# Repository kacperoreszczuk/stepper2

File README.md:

# stepper2
Second version of the lums stepper

Compiling in STM32CubeIDE:

0. Disclaimer: STM32CubeIDE constantly invents new ways to make this instruction not work. Be mentally prepared that you will have to bruteforce this with LLM anyway.
1. Install STM32CubeIDE, sadly requires account creation
2. Click "Import project" and select "fw" directory from this repository
3. In the "Project Explorer" panel on the left open stepper2.ioc
    - confirm "open associated perspecitve" if prompted
    - continue with the current version of the firmware if prompted (do not migrate)
    - Login into MyST account if prompted
    - if not prompted and you get problems later in the instruction in point 4  (more precisely "this project is not a CDT project") then in the stepper2.ioc window click Help->Configuration Tool->Manage Embedded Software Libraries, scroll to STM32H7 and check tick box near version 1.11.1. Click Install. Hopefully you will be prompted to login and the package will install. Continue with instruction (starting here with Project->Generate Code)
    - in the top menu select Project->Generate Code
    - confirm "open associated perspecitve" if prompted
4. go to Project -> Properties -> C/C++ Build -> Settings
    - if "Properties" button is inactive click on main.c file subwindow to focus on it
    - in MCU(or MCU/MPU) Settings  check both "Use float..." options
    - in "MCU Post build outputs" enable binary file (or "convert to binary file")
    - in MCU(or MCU/MPU) GCC Compiler->Optimization: change level to -O3
    - in MCU(or MCU/MPU) G++ Compiler->Optimization: change level to -O3
    - If you want to switch to release configuration, change configuration to Release in the top of the Settings window, and repeat last four steps. In that case take care to build in the release later.
    - click apply and close, confirm if prompted to rebuild index
5. You may want to go to Core/Inc/defaults.hpp and change #define DRIVER_ID to a different value (any you like), especially if you would use more than one device simultaneously and want to be able to discern between them when talking through serial port.
6. Power up the driver and connect it with micro usb port (near the power input socket, slightly lower). Click Run->Run or click the green arrow icon to build and flash the device.
    - You may be prompted to upgrade the stlink firmware. Agree. In the STLinkUpgrade Window click "Open in update mode" and then "Upgrade". Unplug and plug the micro USB cable and try again number 6 in this instruction.
    - you may be prompted to save the files you edited. Agree.
7. Alternatively to point 6. you can select Project->Build Project and then copy manually the file in Debug/stepper2.bin to the mass storage device that opens after conneting the driver.

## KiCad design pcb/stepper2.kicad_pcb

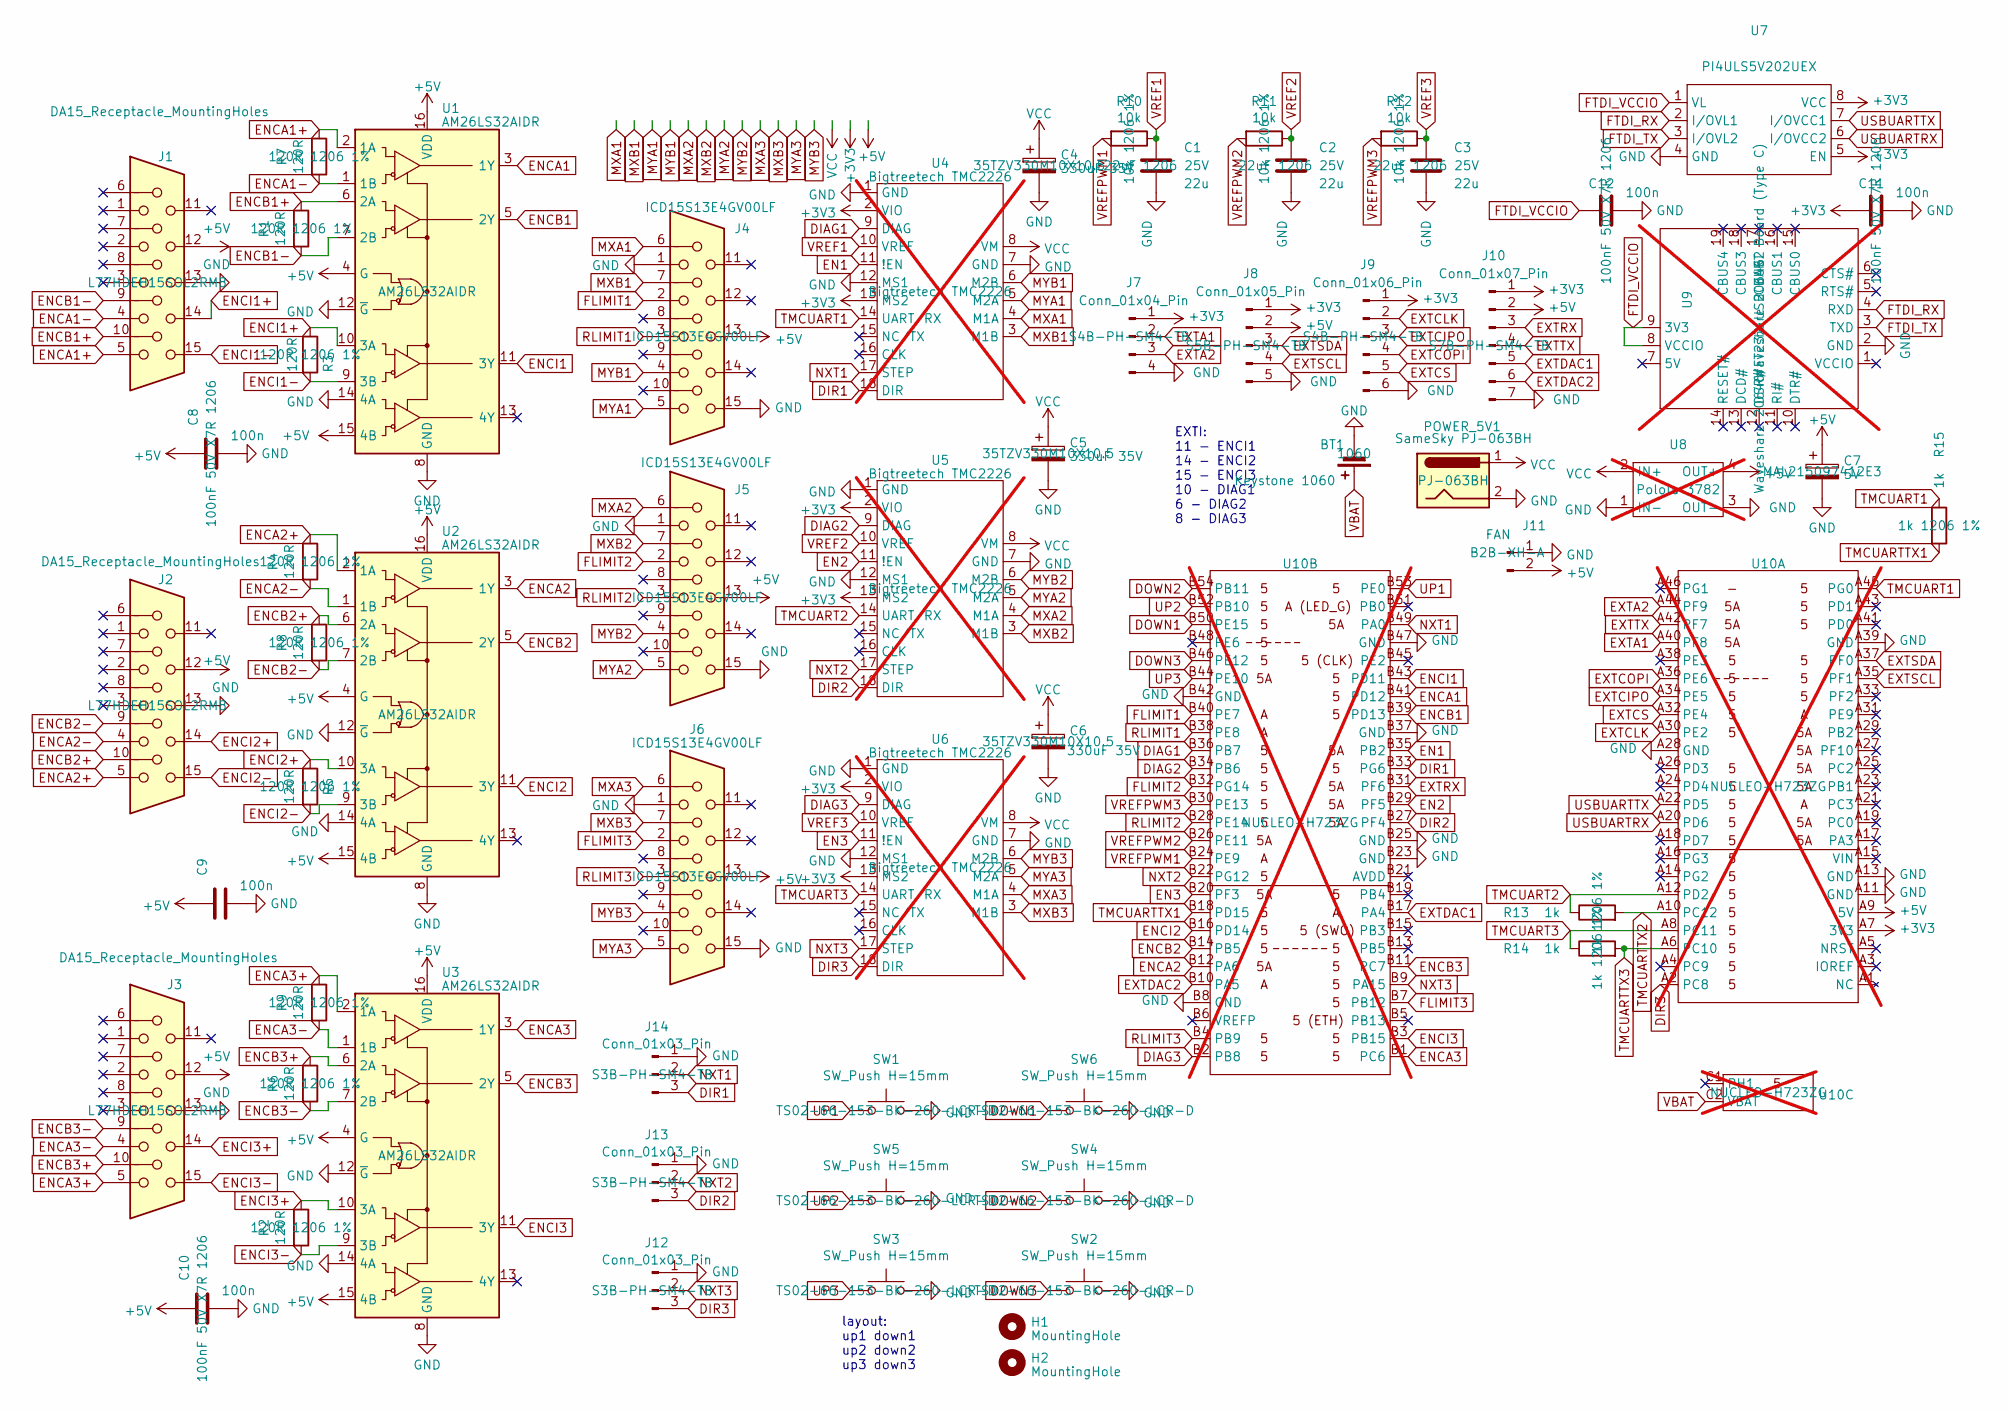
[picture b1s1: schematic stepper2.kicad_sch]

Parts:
BT1: Keystone 1060; BatteryHolder_Keystone_1060_1x2032; mpn 1060
C1, C2, C3: 22u; C_1206_3216Metric_Pad1.33x1.80mm_HandSolder; mpn 22uF 1206 25V; LCSC C12891
C4, C5, C6: 330uF 35V; CP_Elec_10x10.5; mpn 35TZV330M10X10.5; LCSC C2880403
C7: 5V; CP_Elec_8x10.5; mpn MAL215097412E3; LCSC C310836
C8, C9, C10, C11, C12: 100n; C_1206_3216Metric_Pad1.33x1.80mm_HandSolder; mpn 100nF 50V X7R 1206; LCSC C24497
H1, H2: MountingHole; MountingHole_3.2mm_M3
J1, J2, J3: DA15_Receptacle_MountingHoles; DSUB-15-HD_Vertical_Pitch2.29x1.98mm_Mercury3000_Enc; mpn L77HDEH15SOL2RM8
J4, J5, J6: ICD15S13E4GV00LF; DSUB-15-HD_Horizontal_Pitch2.29x2.54mm_EdgePinOffset9.40mm; mpn ICD15S13E4GV00LF
J7: Conn_01x04_Pin; JST_PH_S4B-PH-SM4-TB_1x04-1MP_P2.00mm_Horizontal; mpn S4B-PH-SM4-TB; LCSC C265102
J8: Conn_01x05_Pin; JST_PH_S5B-PH-SM4-TB_1x05-1MP_P2.00mm_Horizontal; mpn S5B-PH-SM4-TB; LCSC C265104
J9: Conn_01x06_Pin; JST_PH_S6B-PH-SM4-TB_1x06-1MP_P2.00mm_Horizontal; mpn S4B-PH-SM4-TB; LCSC C265405
J10: Conn_01x07_Pin; JST_PH_S7B-PH-SM4-TB_1x07-1MP_P2.00mm_Horizontal; mpn S7B-PH-SM4-TB; LCSC C265453
J11: FAN; JST_XH_B2B-XH-AM_1x02_P2.50mm_Vertical; mpn B2B-XH-A
J12, J13, J14: Conn_01x03_Pin; JST_PH_S3B-PH-SM4-TB_1x03-1MP_P2.00mm_Horizontal; mpn S3B-PH-SM4-TB; LCSC C265101
POWER_5V1: SameSky PJ-063BH; BarrelJack_CUI_PJ-063AH_Horizontal_CircularHoles; mpn PJ-063BH
R1, R2, R3, R4, R5, R6, R7, R8, R9: 120R; R_1206_3216Metric_Pad1.30x1.75mm_HandSolder; mpn 120R 1206 1%; LCSC C17909
R10, R11, R12: 10k; R_1206_3216Metric_Pad1.30x1.75mm_HandSolder; mpn 10k 1206 1%; LCSC C17902
R13, R14, R15: 1k; R_1206_3216Metric_Pad1.30x1.75mm_HandSolder; mpn 1k 1206 1%; LCSC C4410
SW1, SW2, SW3, SW4, SW5, SW6: SW_Push H=15mm; SW_PUSH_6mm_H4.3mm; mpn TS02-66-153-BK-260-LCR-D
U1, U2, U3: AM26LS32AIDR; SO-16_3.9x9.9mm_P1.27mm; mpn AM26LS32AIDR; LCSC C19092
U4, U5, U6: Bigtreetech TMC2226; TMC2209_BIGTREETECH; mpn Bigtreetech TMC2226; not fitted
U7: MSOP-8_3x3mm_P0.65mm; mpn PI4ULS5V202UEX; LCSC C481697
U8: POLOLU_3782; mpn Pololu 3782; not fitted
U9: Waveshare 20646 FT232 USB UART Board (Type C); Waveshare_FT232_USBC_module; mpn Waveshare 20646; not fitted
U10: Nucleo144_H723_withVBAT; mpn NUCLEO-H723ZG; not fitted

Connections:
+3V3: C11.1, J7.1, J8.1, J9.1, J10.1, U4.2 (VIO), U4.13 (MS2), U5.2 (VIO), U5.13 (MS2), U6.2 (VIO), U6.13 (MS2), U7.5 (EN), U7.8 (VCC), U10.A7 (3V3)
+5V: C7.1, C8.1, C9.1, C10.1, J1.12, J2.12, J3.12, J4.13, J5.13, J6.13, J8.2, J10.2, J11.2, U1.4 (G), U1.15 (4B), U1.16 (VDD), U2.4 (G), U2.15 (4B), U2.16 (VDD), U3.4 (G), U3.15 (4B), U3.16 (VDD), U8.4 (OUT+), U10.A9 (5V)
DIAG1: U4.9 (DIAG), U10.B36 (PB7)
DIAG2: U5.9 (DIAG), U10.B34 (PB6)
DIAG3: U6.9 (DIAG), U10.B2 (PB8)
DIR1: J14.3, U4.18 (DIR), U10.B33 (PG6)
DIR2: J13.3, U5.18 (DIR), U10.B27 (PF4)
DIR3: J12.3, U6.18 (DIR), U10.A2 (PC8)
DOWN1: SW6.1, U10.B50 (PE15)
DOWN2: SW4.1, U10.B54 (PB11)
DOWN3: SW2.1, U10.B46 (PE12)
EN1: U4.11 (!EN), U10.B35 (PB2)
EN2: U5.11 (!EN), U10.B29 (PF5)
EN3: U6.11 (!EN), U10.B20 (PF3)
ENCA1: U1.3 (1Y), U10.B41 (PD12)
ENCA1+: J1.5, R7.1, U1.2 (1A)
ENCA1-: J1.4, R7.2, U1.1 (1B)
ENCA2: U2.3 (1Y), U10.B12 (PA6)
ENCA2+: J2.5, R4.1, U2.2 (1A)
ENCA2-: J2.4, R4.2, U2.1 (1B)
ENCA3: U3.3 (1Y), U10.B1 (PC6)
ENCA3+: J3.5, R9.1, U3.2 (1A)
ENCA3-: J3.4, R9.2, U3.1 (1B)
ENCB1: U1.5 (2Y), U10.B39 (PD13)
ENCB1+: J1.10, R1.1, U1.6 (2A)
ENCB1-: J1.9, R1.2, U1.7 (2B)
ENCB2: U2.5 (2Y), U10.B14 (PB5)
ENCB2+: J2.10, R8.1, U2.6 (2A)
ENCB2-: J2.9, R8.2, U2.7 (2B)
ENCB3: U3.5 (2Y), U10.B11 (PC7)
ENCB3+: J3.10, R6.1, U3.6 (2A)
ENCB3-: J3.9, R6.2, U3.7 (2B)
ENCI1: U1.11 (3Y), U10.B43 (PD11)
ENCI1+: J1.14, R3.1, U1.10 (3A)
ENCI1-: J1.15, R3.2, U1.9 (3B)
ENCI2: U2.11 (3Y), U10.B16 (PD14)
ENCI2+: J2.14, R5.1, U2.10 (3A)
ENCI2-: J2.15, R5.2, U2.9 (3B)
ENCI3: U3.11 (3Y), U10.B3 (PB15)
ENCI3+: J3.14, R2.1, U3.10 (3A)
ENCI3-: J3.15, R2.2, U3.9 (3B)
EXTA1: J7.2, U10.A40 (PF8)
EXTA2: J7.3, U10.A44 (PF9)
EXTCIPO: J9.3, U10.A34 (PE5)
EXTCLK: J9.2, U10.A30 (PE2)
EXTCOPI: J9.4, U10.A36 (PE6)
EXTCS: J9.5, U10.A32 (PE4)
EXTDAC1: J10.5, U10.B17 (PA4)
EXTDAC2: J10.6, U10.B10 (PA5)
EXTRX: J10.3, U10.B31 (PF6)
EXTSCL: J8.4, U10.A35 (PF1)
EXTSDA: J8.3, U10.A37 (PF0)
EXTTX: J10.4, U10.A42 (PF7)
FLIMIT1: J4.2, U10.B40 (PE7)
FLIMIT2: J5.2, U10.B32 (PG14)
FLIMIT3: J6.2, U10.B7 (PB12)
FTDI_RX: U7.2 (I/OVL1), U9.4 (RXD)
FTDI_TX: U7.3 (I/OVL2), U9.3 (TXD)
FTDI_VCCIO: C12.1, U7.1 (VL), U9.8 (VCCIO), U9.9 (3V3)
GND: BT1.2 (-), C1.2, C2.2, C3.2, C4.2, C5.2, C6.2, C7.2, C8.2, C9.2, C10.2, C11.2, C12.2, J1.13, J2.13, J3.13, J4.1, J4.15, J5.1, J5.15, J6.1, J6.15, J7.4, J8.5, J9.6, J10.7, J11.1, J12.1, J13.1, J14.1, POWER_5V1.2, SW1.2, SW2.2, SW3.2, SW4.2, SW5.2, SW6.2, U1.8 (GND), U1.12 (~G), U1.14 (4A), U2.8 (GND), U2.12 (~G), U2.14 (4A), U3.8 (GND), U3.12 (~G), U3.14 (4A), U4.1 (GND), U4.7 (GND), U4.12 (MS1), U5.1 (GND), U5.7 (GND), U5.12 (MS1), U6.1 (GND), U6.7 (GND), U6.12 (MS1), U7.4 (GND), U8.1 (IN-), U8.3 (OUT-), U9.2 (GND), U10.A11 (GND), U10.A13 (GND), U10.A28 (GND), U10.A39 (GND), U10.B8 (GND), U10.B23 (GND), U10.B25 (GND), U10.B37 (GND), U10.B42 (GND), U10.B47 (GND)
MXA1: J4.6, U4.4 (M1A)
MXA2: J5.6, U5.4 (M1A)
MXA3: J6.6, U6.4 (M1A)
MXB1: J4.7, U4.3 (M1B)
MXB2: J5.7, U5.3 (M1B)
MXB3: J6.7, U6.3 (M1B)
MYA1: J4.5, U4.5 (M2A)
MYA2: J5.5, U5.5 (M2A)
MYA3: J6.5, U6.5 (M2A)
MYB1: J4.4, U4.6 (M2B)
MYB2: J5.4, U5.6 (M2B)
MYB3: J6.4, U6.6 (M2B)
NXT1: J14.2, U4.17 (STEP), U10.B49 (PA0)
NXT2: J13.2, U5.17 (STEP), U10.B22 (PG12)
NXT3: J12.2, U6.17 (STEP), U10.B9 (PA15)
RLIMIT1: J4.3, U10.B38 (PE8)
RLIMIT2: J5.3, U10.B28 (PE14)
RLIMIT3: J6.3, U10.B4 (PB9)
TMCUART1: R15.1, U4.14 (UART/RX), U10.A45 (PG0)
TMCUART2: R13.1, U5.14 (UART/RX), U10.A12 (PD2)
TMCUART3: R14.1, U6.14 (UART/RX), U10.A8 (PC11)
TMCUARTTX1: R15.2, U10.B18 (PD15)
TMCUARTTX2: R13.2, U10.A10 (PC12)
TMCUARTTX3: R14.2, U10.A6 (PC10)
UP1: SW1.1, U10.B53 (PE0)
UP2: SW5.1, U10.B52 (PB10)
UP3: SW3.1, U10.B44 (PE10)
USBUARTRX: U7.6 (I/OVCC2), U10.A20 (PD6)
USBUARTTX: U7.7 (I/OVCC1), U10.A22 (PD5)
VBAT: BT1.1 (+), U10.C2 (VBAT)
VCC: C4.1, C5.1, C6.1, POWER_5V1.1, U4.8 (VM), U5.8 (VM), U6.8 (VM), U8.2 (IN+)
VREF1: C1.1, R10.1, U4.10 (VREF)
VREF2: C2.1, R11.1, U5.10 (VREF)
VREF3: C3.1, R12.1, U6.10 (VREF)
VREFPWM1: R10.2, U10.B24 (PE9)
VREFPWM2: R11.2, U10.B26 (PE11)
VREFPWM3: R12.2, U10.B30 (PE13)

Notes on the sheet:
layout: up1 down1 up2 down2 up3 down3
EXTI: 11 - ENCI1 14 - ENCI2 15 - ENCI3 10 - DIAG1 6 - DIAG2 8 - DIAG3

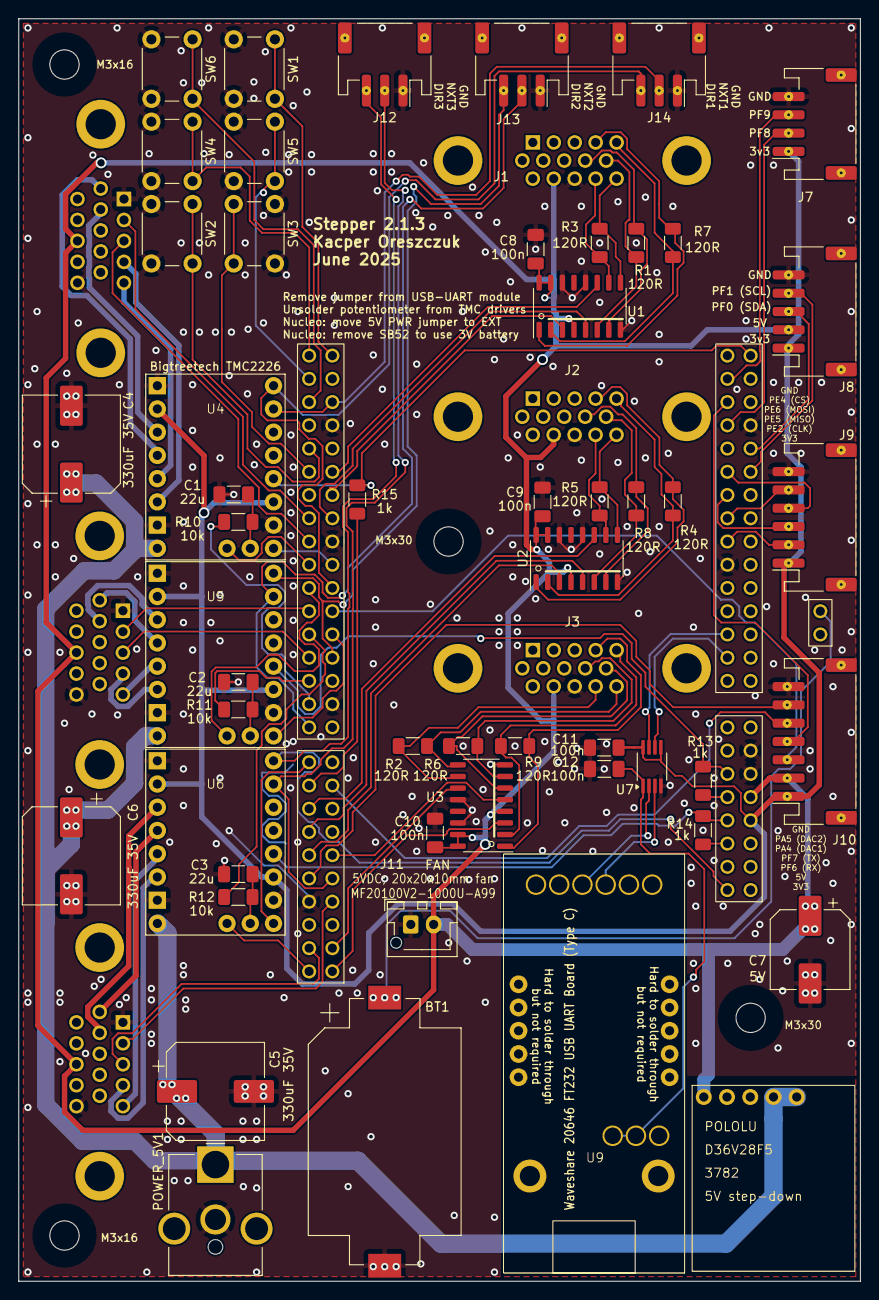
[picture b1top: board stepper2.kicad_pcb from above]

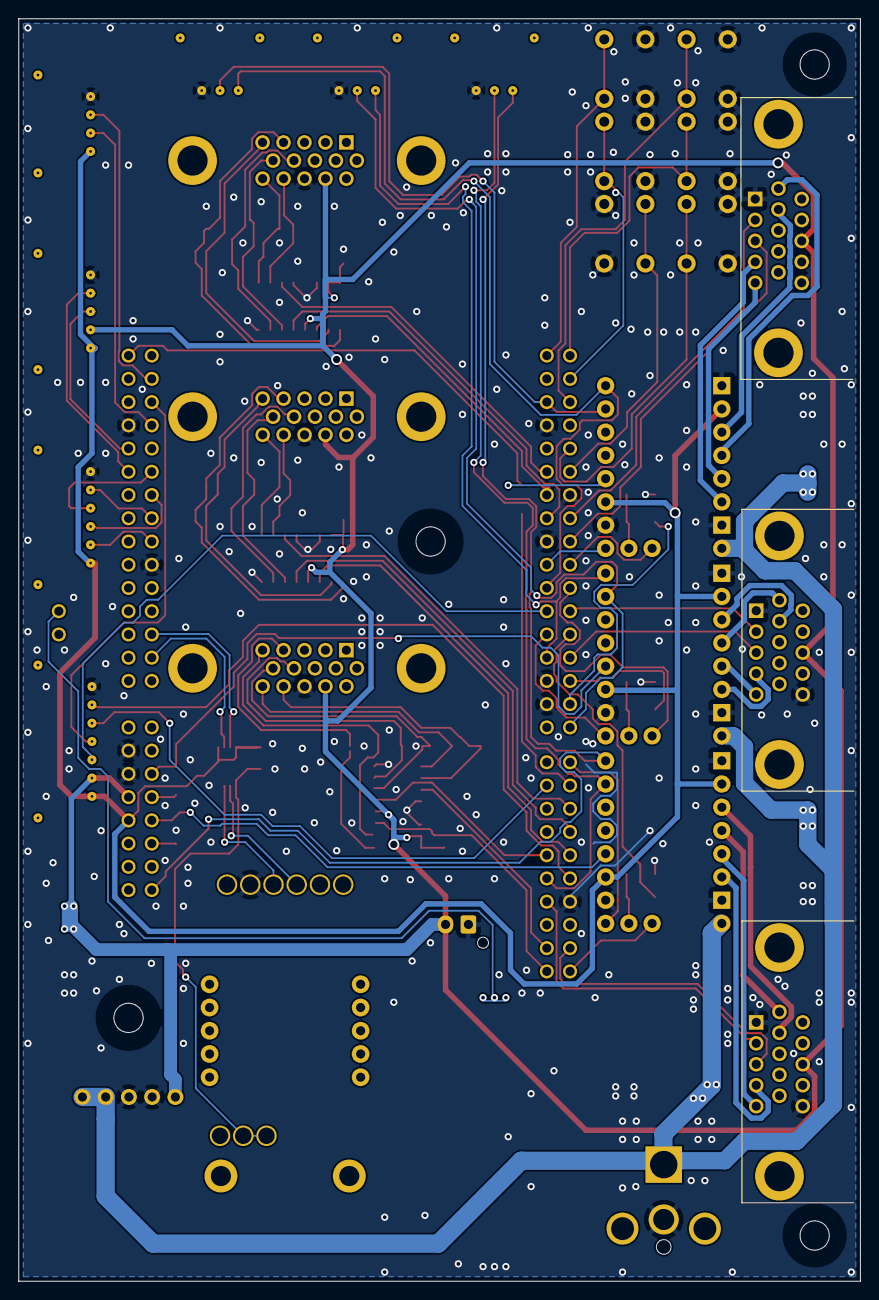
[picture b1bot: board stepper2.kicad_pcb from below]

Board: 2 copper layers, 92.0 x 138.0 mm, 61 parts (3 on the bottom side), 97 nets.

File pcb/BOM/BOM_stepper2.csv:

Comment,Designator,Footprint,LCSC
3V,BT1,Battery:BatteryHolder_Keystone_1060_1x2032,
22u,C1,Capacitor_SMD:C_1206_3216Metric_Pad1.33x1.80mm_HandSolder,C12891
22u,C2,Capacitor_SMD:C_1206_3216Metric_Pad1.33x1.80mm_HandSolder,C12891
22u,C3,Capacitor_SMD:C_1206_3216Metric_Pad1.33x1.80mm_HandSolder,C12891
24V,C4,Capacitor_SMD:CP_Elec_10x10.5,C5155335
24V,C5,Capacitor_SMD:CP_Elec_10x10.5,C5155335
24V,C6,Capacitor_SMD:CP_Elec_10x10.5,C5155335
5V,C7,Capacitor_SMD:CP_Elec_8x10.5,C310836
100n,C8,Capacitor_SMD:C_1206_3216Metric_Pad1.33x1.80mm_HandSolder,C24497
100n,C9,Capacitor_SMD:C_1206_3216Metric_Pad1.33x1.80mm_HandSolder,C24497
100n,C10,Capacitor_SMD:C_1206_3216Metric_Pad1.33x1.80mm_HandSolder,C24497
100n,C11,Capacitor_SMD:C_1206_3216Metric_Pad1.33x1.80mm_HandSolder,C24497
100n,C12,Capacitor_SMD:C_1206_3216Metric_Pad1.33x1.80mm_HandSolder,C24497
MountingHole,H1,stepper2:MountingHole_3.2mm_M3,
MountingHole,H2,stepper2:MountingHole_3.2mm_M3,
DA15_Receptacle_MountingHoles,J1,stepper2:DSUB-15-HD_Vertical_Pitch2.29x1.98mm_Mercury3000_Enc,
DA15_Receptacle_MountingHoles,J2,stepper2:DSUB-15-HD_Vertical_Pitch2.29x1.98mm_Mercury3000_Enc,
DA15_Receptacle_MountingHoles,J3,stepper2:DSUB-15-HD_Vertical_Pitch2.29x1.98mm_Mercury3000_Enc,
DE15_Receptacle_HighDensity,J4,stepper2:DSUB-15-HD_Horizontal_Pitch2.29x2.54mm_EdgePinOffset9.40mm,
DE15_Receptacle_HighDensity,J5,stepper2:DSUB-15-HD_Horizontal_Pitch2.29x2.54mm_EdgePinOffset9.40mm,
DE15_Receptacle_HighDensity,J6,stepper2:DSUB-15-HD_Horizontal_Pitch2.29x2.54mm_EdgePinOffset9.40mm,
Conn_01x04_Pin,J7,stepper2:JST_PH_S4B-PH-SM4-TB_1x04-1MP_P2.00mm_Horizontal,C265102
Conn_01x05_Pin,J8,stepper2:JST_PH_S5B-PH-SM4-TB_1x05-1MP_P2.00mm_Horizontal,C265104
Conn_01x06_Pin,J9,stepper2:JST_PH_S6B-PH-SM4-TB_1x06-1MP_P2.00mm_Horizontal,C265405
Conn_01x07_Pin,J10,stepper2:JST_PH_S7B-PH-SM4-TB_1x07-1MP_P2.00mm_Horizontal,C265453
FAN,J11,Connector_JST:JST_XH_B2B-XH-AM_1x02_P2.50mm_Vertical,
Conn_01x03_Pin,J12,stepper2:JST_PH_S3B-PH-SM4-TB_1x03-1MP_P2.00mm_Horizontal,C265101
Conn_01x03_Pin,J13,stepper2:JST_PH_S3B-PH-SM4-TB_1x03-1MP_P2.00mm_Horizontal,C265101
Conn_01x03_Pin,J14,stepper2:JST_PH_S3B-PH-SM4-TB_1x03-1MP_P2.00mm_Horizontal,C265101
Jack-DC,POWER_5V1,Connector_BarrelJack:BarrelJack_CUI_PJ-063AH_Horizontal_CircularHoles,
120R,R1,Resistor_SMD:R_1206_3216Metric_Pad1.30x1.75mm_HandSolder,C17909
120R,R2,Resistor_SMD:R_1206_3216Metric_Pad1.30x1.75mm_HandSolder,C17909
120R,R3,Resistor_SMD:R_1206_3216Metric_Pad1.30x1.75mm_HandSolder,C17909
120R,R4,Resistor_SMD:R_1206_3216Metric_Pad1.30x1.75mm_HandSolder,C17909
120R,R5,Resistor_SMD:R_1206_3216Metric_Pad1.30x1.75mm_HandSolder,C17909
120R,R6,Resistor_SMD:R_1206_3216Metric_Pad1.30x1.75mm_HandSolder,C17909
120R,R7,Resistor_SMD:R_1206_3216Metric_Pad1.30x1.75mm_HandSolder,C17909
120R,R8,Resistor_SMD:R_1206_3216Metric_Pad1.30x1.75mm_HandSolder,C17909
120R,R9,Resistor_SMD:R_1206_3216Metric_Pad1.30x1.75mm_HandSolder,C17909
10k,R10,Resistor_SMD:R_1206_3216Metric_Pad1.30x1.75mm_HandSolder,C17902
10k,R11,Resistor_SMD:R_1206_3216Metric_Pad1.30x1.75mm_HandSolder,C17902
10k,R12,Resistor_SMD:R_1206_3216Metric_Pad1.30x1.75mm_HandSolder,C17902
1k,R13,Resistor_SMD:R_1206_3216Metric_Pad1.30x1.75mm_HandSolder,C4410
1k,R14,Resistor_SMD:R_1206_3216Metric_Pad1.30x1.75mm_HandSolder,C4410
1k,R15,Resistor_SMD:R_1206_3216Metric_Pad1.30x1.75mm_HandSolder,C4410
SW_Push,SW1,Button_Switch_SMD:SW_Push_1P1T_NO_6x6mm_H9.5mm,C620327
SW_Push,SW2,Button_Switch_SMD:SW_Push_1P1T_NO_6x6mm_H9.5mm,C620327
SW_Push,SW3,Button_Switch_SMD:SW_Push_1P1T_NO_6x6mm_H9.5mm,C620327
SW_Push,SW4,Button_Switch_SMD:SW_Push_1P1T_NO_6x6mm_H9.5mm,C620327
SW_Push,SW5,Button_Switch_SMD:SW_Push_1P1T_NO_6x6mm_H9.5mm,C620327
SW_Push,SW6,Button_Switch_SMD:SW_Push_1P1T_NO_6x6mm_H9.5mm,C620327
AM26LS32ACN,U1,stepper2:SO-16_3.9x9.9mm_P1.27mm,C19092
AM26LS32ACN,U2,stepper2:SO-16_3.9x9.9mm_P1.27mm,C19092
AM26LS32ACN,U3,stepper2:SO-16_3.9x9.9mm_P1.27mm,C19092
TMC2209_BIGTREETECH,U4,stepper2:TMC2209_BIGTREETECH,
TMC2209_BIGTREETECH,U5,stepper2:TMC2209_BIGTREETECH,
TMC2209_BIGTREETECH,U6,stepper2:TMC2209_BIGTREETECH,
~,U7,stepper2:UDFN-8_1.2x1.8mm_OR_SO8_3.9x4.9mm,C725710
~,U8,stepper2:DCDC_17.0mm_22.2mm,
~,U9,stepper2:Waveshare_FT232_USBC_module,
~,U10,stepper2:Nucleo144_H723_withVBAT,

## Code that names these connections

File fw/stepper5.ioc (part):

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Mcu.Name=STM32H723ZGTx
Mcu.Package=LQFP144
Mcu.UserName=STM32H723ZGTx
PA0.GPIOParameters=GPIO_Label
PA0.GPIO_Label=NXT1
PA0.Signal=S_TIM5_CH1
PA1.GPIOParameters=GPIO_Label
PA1.GPIO_Label=RMII_REF_CLK
PA1.Mode=RMII
PA1.Signal=ETH_REF_CLK
PA10.GPIOParameters=GPIO_Label
PA10.GPIO_Label=USB_FS_ID
PA10.Mode=OTG/Dual-Role-Device-FS
PA10.Signal=USB_OTG_HS_ID
PA11.GPIOParameters=GPIO_Label
PA11.GPIO_Label=USB_FS_DM
PA11.Mode=OTG/Dual-Role-Device-FS
PA11.Signal=USB_OTG_HS_DM
PA12.GPIOParameters=GPIO_Label
PA12.GPIO_Label=USB_FS_DP
PA12.Mode=OTG/Dual-Role-Device-FS
PA12.Signal=USB_OTG_HS_DP
PA13(JTMS/SWDIO).GPIOParameters=GPIO_Label
PA13(JTMS/SWDIO).GPIO_Label=SWDIO
PA13(JTMS/SWDIO).Mode=Trace_Asynchronous_SW
PA13(JTMS/SWDIO).Signal=DEBUG_JTMS-SWDIO
PA14(JTCK/SWCLK).GPIOParameters=GPIO_Label
PA14(JTCK/SWCLK).GPIO_Label=SWCLK
PA14(JTCK/SWCLK).Mode=Trace_Asynchronous_SW
PA14(JTCK/SWCLK).Signal=DEBUG_JTCK-SWCLK
PA15(JTDI).GPIOParameters=GPIO_Label
PA15(JTDI).GPIO_Label=NXT3
PA15(JTDI).Signal=S_TIM2_CH1_ETR
PA2.GPIOParameters=GPIO_Label
PA2.GPIO_Label=RMII_MDIO
PA2.Mode=RMII
PA2.Signal=ETH_MDIO
PA4.GPIOParameters=GPIO_Label
PA4.GPIO_Label=EXTDAC1
PA4.Signal=COMP_DAC11_group
PA5.GPIOParameters=GPIO_Label
PA5.GPIO_Label=EXTDAC2
PA5.Signal=COMP_DAC12_group
PA6.GPIOParameters=GPIO_Label
PA6.GPIO_Label=ENCA2
PA6.Signal=S_TIM3_CH1
PA7.GPIOParameters=GPIO_Label
PA7.GPIO_Label=RMII_CRS_DV
PA7.Mode=RMII
PA7.Signal=ETH_CRS_DV
PA9.GPIOParameters=GPIO_Label
PA9.GPIO_Label=USB_FS_VBUS
PA9.Mode=Activate_VBUS_FS
PA9.Signal=USB_OTG_HS_VBUS
PB0.GPIOParameters=GPIO_Label
PB0.GPIO_Label=LED_GREEN
PB0.Signal=GPIO_Output
PB10.GPIOParameters=GPIO_Label
PB10.GPIO_Label=DOWN2
PB10.Signal=GPIO_Input
PB11.GPIOParameters=GPIO_Label
PB11.GPIO_Label=DOWN1
PB11.Signal=GPIO_Input
PB12.GPIOParameters=GPIO_Label
PB12.GPIO_Label=FLIMIT3
PB12.Signal=GPIO_Input
PB13.GPIOParameters=GPIO_Label
PB13.GPIO_Label=RMII_TXD1
PB13.Mode=RMII
PB13.Signal=ETH_TXD1
PB14.GPIOParameters=GPIO_Label
PB14.GPIO_Label=LED_RED
PB14.Signal=GPIO_Output
PB15.GPIOParameters=GPIO_Label
PB15.GPIO_Label=ENCI3
PB15.Signal=GPXTI15
PB2.GPIOParameters=GPIO_Label
PB2.GPIO_Label=EN1
PB2.Signal=GPIO_Output
PB3(JTDO/TRACESWO).GPIOParameters=GPIO_Label
PB3(JTDO/TRACESWO).GPIO_Label=SWO
PB3(JTDO/TRACESWO).Mode=Trace_Asynchronous_SW
PB3(JTDO/TRACESWO).Signal=DEBUG_JTDO-SWO
PB5.GPIOParameters=GPIO_Label
PB5.GPIO_Label=ENCB2
PB5.Signal=S_TIM3_CH2
PB6.GPIOParameters=GPIO_Label
PB6.GPIO_Label=DIAG2
PB6.Signal=GPXTI6
PB7.GPIOParameters=GPIO_Label
PB7.GPIO_Label=DIAG1
PB7.Signal=GPXTI7
PB8.GPIOParameters=GPIO_Label
PB8.GPIO_Label=DIAG3
PB8.Signal=GPXTI8
PB9.GPIOParameters=GPIO_Label
PB9.GPIO_Label=RLIMIT3
PB9.Signal=GPIO_Input
PC1.GPIOParameters=GPIO_Label
PC1.GPIO_Label=RMII_MDC
PC1.Mode=RMII
PC1.Signal=ETH_MDC
PC10.GPIOParameters=GPIO_Label
PC10.GPIO_Label=TMCUARTTX3
PC10.Mode=Asynchronous
PC10.Signal=UART4_TX
PC11.GPIOParameters=GPIO_Label
PC11.GPIO_Label=TMCUARTRX3
PC11.Mode=Asynchronous
PC11.Signal=UART4_RX
PC12.GPIOParameters=GPIO_Label
PC12.GPIO_Label=TMCUARTTX2
PC12.Mode=Asynchronous
PC12.Signal=UART5_TX
PC13.GPIOParameters=GPIO_Label
PC13.GPIO_Label=B1 (Blue_User_Button)
PC13.Signal=GPIO_Input
PC14-OSC32_IN.Mode=LSE-External-Oscillator
PC14-OSC32_IN.Signal=RCC_OSC32_IN
PC15-OSC32_OUT.Mode=LSE-External-Oscillator
PC15-OSC32_OUT.Signal=RCC_OSC32_OUT
PC4.GPIOParameters=GPIO_Label
PC4.GPIO_Label=RMII_RXD0
PC4.Mode=RMII
PC4.Signal=ETH_RXD0
PC5.GPIOParameters=GPIO_Label
PC5.GPIO_Label=RMII_RXD1
PC5.Mode=RMII
PC5.Signal=ETH_RXD1
PC6.GPIOParameters=GPIO_Label
PC6.GPIO_Label=ENCA3
PC6.Signal=S_TIM8_CH1
PC7.GPIOParameters=GPIO_Label
PC7.GPIO_Label=ENCB3
PC7.Signal=S_TIM8_CH2
PC8.GPIOParameters=GPIO_Label
PC8.GPIO_Label=DIR3
PC8.Signal=GPIO_Output
PD10.Signal=GPIO_Output
PD12.GPIOParameters=GPIO_Label
PD12.GPIO_Label=ENCA1
PD12.Signal=S_TIM4_CH1
PD13.GPIOParameters=GPIO_Label
PD13.GPIO_Label=ENCB1
PD13.Signal=S_TIM4_CH2
PD14.GPIOParameters=GPIO_Label
PD14.GPIO_Label=ENCI2
PD14.Signal=GPXTI14
PD15.GPIOParameters=GPIO_Label
PD15.GPIO_Label=TMCUARTTX1
PD15.Mode=Asynchronous
PD15.Signal=UART9_TX
PD2.GPIOParameters=GPIO_Label
PD2.GPIO_Label=TMCUARTRX2
PD2.Mode=Asynchronous
PD2.Signal=UART5_RX
PD5.GPIOParameters=GPIO_Label
PD5.GPIO_Label=USBUARTTX
PD5.Mode=Asynchronous
PD5.Signal=USART2_TX
PD6.GPIOParameters=GPIO_Label
PD6.GPIO_Label=USBUARTRX
PD6.Mode=Asynchronous
PD6.Signal=USART2_RX
PD8.GPIOParameters=GPIO_Label
PD8.GPIO_Label=STLK_VCP_RX
PD8.Mode=Asynchronous
PD8.Signal=USART3_TX
PD9.GPIOParameters=GPIO_Label
PD9.GPIO_Label=STLK_VCP_TX
PD9.Mode=Asynchronous
PD9.Signal=USART3_RX
PE0.GPIOParameters=GPIO_Label
PE0.GPIO_Label=UP1
PE0.Signal=GPIO_Input
PE1.GPIOParameters=GPIO_Label
PE1.GPIO_Label=LED_YELLOW
PE1.Signal=GPIO_Output
PE10.GPIOParameters=GPIO_Label
PE10.GPIO_Label=UP3
PE10.Signal=GPIO_Input
PE11.GPIOParameters=GPIO_Label
PE11.GPIO_Label=VREFPWM2
PE11.Signal=S_TIM1_CH2
PE12.GPIOParameters=GPIO_Label
PE12.GPIO_Label=UP2
PE12.Signal=GPIO_Input
PE13.GPIOParameters=GPIO_Label
PE13.GPIO_Label=VREFPWM3
PE13.Signal=S_TIM1_CH3
PE14.GPIOParameters=GPIO_Label
PE14.GPIO_Label=RLIMIT2
PE14.Signal=GPIO_Input
PE15.GPIOParameters=GPIO_Label
PE15.GPIO_Label=DOWN3
PE15.Signal=GPIO_Input
PE2.GPIOParameters=GPIO_Label
PE2.GPIO_Label=EXTCLK
PE2.Mode=Full_Duplex_Master
PE2.Signal=SPI4_SCK
PE4.GPIOParameters=GPIO_Label
PE4.GPIO_Label=EXTCS
PE4.Mode=NSS_Signal_Hard_Output
PE4.Signal=SPI4_NSS
PE5.GPIOParameters=GPIO_Label
PE5.GPIO_Label=EXTCIPO
PE5.Mode=Full_Duplex_Master
PE5.Signal=SPI4_MISO
PE6.GPIOParameters=GPIO_Label
PE6.GPIO_Label=EXTCOPI
PE6.Mode=Full_Duplex_Master
PE6.Signal=SPI4_MOSI
PE7.GPIOParameters=GPIO_Label
PE7.GPIO_Label=FLIMIT1
PE7.Signal=GPIO_Input
PE8.GPIOParameters=GPIO_Label
PE8.GPIO_Label=RLIMIT1
PE8.Signal=GPIO_Input
PE9.GPIOParameters=GPIO_Label
PE9.GPIO_Label=VREFPWM1
PE9.Signal=S_TIM1_CH1
PF0.GPIOParameters=GPIO_Label
PF0.GPIO_Label=EXTSDA
PF0.Mode=I2C
PF0.Signal=I2C5_SDA
PF1.GPIOParameters=GPIO_Label
PF1.GPIO_Label=EXTSCL
PF1.Mode=I2C
PF1.Signal=I2C5_SCL
PF3.GPIOParameters=GPIO_Label
PF3.GPIO_Label=EN3
PF3.Signal=GPIO_Output
PF4.GPIOParameters=GPIO_Label
PF4.GPIO_Label=DIR2
PF4.Signal=GPIO_Output
PF5.GPIOParameters=GPIO_Label
PF5.GPIO_Label=EN2
PF5.Signal=GPIO_Output
PF6.GPIOParameters=GPIO_Label
PF6.GPIO_Label=EXTRXUART
PF6.Mode=Asynchronous
PF6.Signal=UART7_RX
PF7.GPIOParameters=GPIO_Label
PF7.GPIO_Label=EXTTXUART
PF7.Mode=Asynchronous
PF7.Signal=UART7_TX
PF8.GPIOParameters=GPIO_Label
PF8.GPIO_Label=EXTA1
PF8.Signal=GPIO_Analog
PF9.GPIOParameters=GPIO_Label
PF9.GPIO_Label=EXTA2
PF9.Signal=GPIO_Analog
PG0.GPIOParameters=GPIO_Label
PG0.GPIO_Label=TMCUARTRX1
PG0.Mode=Asynchronous
PG0.Signal=UART9_RX
PG11.GPIOParameters=GPIO_Label
PG11.GPIO_Label=RMII_TX_EN
PG11.Mode=RMII
PG11.Signal=ETH_TX_EN
PG12.GPIOParameters=GPIO_Label
PG12.GPIO_Label=NXT2
PG12.Mode=PWM Generation1 CH1
PG12.Signal=TIM23_CH1
PG13.GPIOParameters=GPIO_Label
PG13.GPIO_Label=RMII_TXD0
PG13.Mode=RMII
PG13.Signal=ETH_TXD0
PG14.GPIOParameters=GPIO_Label
PG14.GPIO_Label=FLIMIT2
PG14.Signal=GPIO_Input
PG6.GPIOParameters=GPIO_Label
PG6.GPIO_Label=DIR1
PG6.Signal=GPIO_Output
PH0-OSC_IN.GPIOParameters=GPIO_Label
PH0-OSC_IN.GPIO_Label=MCO
PH0-OSC_IN.Mode=HSE-External-Clock-Source
PH0-OSC_IN.Signal=RCC_OSC_IN
PH1-OSC_OUT.Signal=RCC_OSC_OUT
RCC.HSE_VALUE=8000000
RCC.SYSCLKFreq_VALUE=550000000
RCC.SYSCLKSource=RCC_SYSCLKSOURCE_PLLCLK
board=NUCLEO-H723ZG
boardIOC=true

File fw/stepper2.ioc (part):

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Mcu.Name=STM32H723ZGTx
Mcu.Package=LQFP144
Mcu.UserName=STM32H723ZGTx
PA0.GPIOParameters=GPIO_Label
PA0.GPIO_Label=NXT1
PA0.Signal=GPIO_Output
PA1.GPIOParameters=GPIO_Label
PA1.GPIO_Label=RMII_REF_CLK
PA1.Mode=RMII
PA1.Signal=ETH_REF_CLK
PA10.GPIOParameters=GPIO_Label
PA10.GPIO_Label=USB_FS_ID
PA10.Mode=OTG/Dual-Role-Device-FS
PA10.Signal=USB_OTG_HS_ID
PA11.GPIOParameters=GPIO_Label
PA11.GPIO_Label=USB_FS_DM
PA11.Mode=OTG/Dual-Role-Device-FS
PA11.Signal=USB_OTG_HS_DM
PA12.GPIOParameters=GPIO_Label
PA12.GPIO_Label=USB_FS_DP
PA12.Mode=OTG/Dual-Role-Device-FS
PA12.Signal=USB_OTG_HS_DP
PA13(JTMS/SWDIO).GPIOParameters=GPIO_Label
PA13(JTMS/SWDIO).GPIO_Label=SWDIO
PA13(JTMS/SWDIO).Mode=Trace_Asynchronous_SW
PA13(JTMS/SWDIO).Signal=DEBUG_JTMS-SWDIO
PA14(JTCK/SWCLK).GPIOParameters=GPIO_Label
PA14(JTCK/SWCLK).GPIO_Label=SWCLK
PA14(JTCK/SWCLK).Mode=Trace_Asynchronous_SW
PA14(JTCK/SWCLK).Signal=DEBUG_JTCK-SWCLK
PA15(JTDI).GPIOParameters=GPIO_Label
PA15(JTDI).GPIO_Label=NXT3
PA15(JTDI).Signal=GPIO_Output
PA2.GPIOParameters=GPIO_Label
PA2.GPIO_Label=RMII_MDIO
PA2.Mode=RMII
PA2.Signal=ETH_MDIO
PA4.GPIOParameters=GPIO_Label
PA4.GPIO_Label=EXTDAC1
PA4.Signal=COMP_DAC11_group
PA5.GPIOParameters=GPIO_Label
PA5.GPIO_Label=EXTDAC2
PA5.Signal=COMP_DAC12_group
PA6.GPIOParameters=GPIO_Label
PA6.GPIO_Label=ENCA2
PA6.Signal=S_TIM3_CH1
PA7.GPIOParameters=GPIO_Label
PA7.GPIO_Label=RMII_CRS_DV
PA7.Mode=RMII
PA7.Signal=ETH_CRS_DV
PA9.GPIOParameters=GPIO_Label
PA9.GPIO_Label=USB_FS_VBUS
PA9.Mode=Activate_VBUS_FS
PA9.Signal=USB_OTG_HS_VBUS
PB0.GPIOParameters=GPIO_Label
PB0.GPIO_Label=LED_GREEN
PB0.Signal=GPIO_Output
PB10.GPIOParameters=GPIO_PuPd,GPIO_Label
PB10.GPIO_Label=FJOG2
PB10.GPIO_PuPd=GPIO_PULLUP
PB10.Signal=GPIO_Input
PB11.GPIOParameters=GPIO_PuPd,GPIO_Label
PB11.GPIO_Label=RJOG2
PB11.GPIO_PuPd=GPIO_PULLUP
PB11.Signal=GPIO_Input
PB12.GPIOParameters=GPIO_Label
PB12.GPIO_Label=FLIMIT3
PB12.Signal=GPIO_Input
PB13.GPIOParameters=GPIO_Label
PB13.GPIO_Label=RMII_TXD1
PB13.Mode=RMII
PB13.Signal=ETH_TXD1
PB14.GPIOParameters=GPIO_Label
PB14.GPIO_Label=LED_RED
PB14.Signal=GPIO_Output
PB15.GPIOParameters=GPIO_Label
PB15.GPIO_Label=ENCI3
PB15.Signal=GPXTI15
PB2.GPIOParameters=GPIO_Label
PB2.GPIO_Label=EN1
PB2.Signal=GPIO_Output
PB3(JTDO/TRACESWO).GPIOParameters=GPIO_Label
PB3(JTDO/TRACESWO).GPIO_Label=SWO
PB3(JTDO/TRACESWO).Mode=Trace_Asynchronous_SW
PB3(JTDO/TRACESWO).Signal=DEBUG_JTDO-SWO
PB5.GPIOParameters=GPIO_Label
PB5.GPIO_Label=ENCB2
PB5.Signal=S_TIM3_CH2
PB6.GPIOParameters=GPIO_Label
PB6.GPIO_Label=DIAG2
PB6.Signal=GPXTI6
PB7.GPIOParameters=GPIO_Label
PB7.GPIO_Label=DIAG1
PB7.Signal=GPXTI7
PB8.GPIOParameters=GPIO_Label
PB8.GPIO_Label=DIAG3
PB8.Signal=GPXTI8
PB9.GPIOParameters=GPIO_Label
PB9.GPIO_Label=RLIMIT3
PB9.Signal=GPIO_Input
PC1.GPIOParameters=GPIO_Label
PC1.GPIO_Label=RMII_MDC
PC1.Mode=RMII
PC1.Signal=ETH_MDC
PC10.GPIOParameters=GPIO_Label
PC10.GPIO_Label=TMCUARTTX3
PC10.Mode=Asynchronous
PC10.Signal=UART4_TX
PC11.GPIOParameters=GPIO_Label
PC11.GPIO_Label=TMCUARTRX3
PC11.Mode=Asynchronous
PC11.Signal=UART4_RX
PC12.GPIOParameters=GPIO_Label
PC12.GPIO_Label=TMCUARTTX2
PC12.Mode=Asynchronous
PC12.Signal=UART5_TX
PC13.GPIOParameters=GPIO_Label
PC13.GPIO_Label=B1 (Blue_User_Button)
PC13.Signal=GPIO_Input
PC14-OSC32_IN.Mode=LSE-External-Oscillator
PC14-OSC32_IN.Signal=RCC_OSC32_IN
PC15-OSC32_OUT.Mode=LSE-External-Oscillator
PC15-OSC32_OUT.Signal=RCC_OSC32_OUT
PC4.GPIOParameters=GPIO_Label
PC4.GPIO_Label=RMII_RXD0
PC4.Mode=RMII
PC4.Signal=ETH_RXD0
PC5.GPIOParameters=GPIO_Label
PC5.GPIO_Label=RMII_RXD1
PC5.Mode=RMII
PC5.Signal=ETH_RXD1
PC6.GPIOParameters=GPIO_Label
PC6.GPIO_Label=ENCA3
PC6.Signal=S_TIM8_CH1
PC7.GPIOParameters=GPIO_Label
PC7.GPIO_Label=ENCB3
PC7.Signal=S_TIM8_CH2
PC8.GPIOParameters=GPIO_Label
PC8.GPIO_Label=DIR3
PC8.Signal=GPIO_Output
PD10.Signal=GPIO_Output
PD11.GPIOParameters=GPIO_Label
PD11.GPIO_Label=ENCI1
PD11.Signal=GPIO_Input
PD12.GPIOParameters=GPIO_Label
PD12.GPIO_Label=ENCA1
PD12.Signal=S_TIM4_CH1
PD13.GPIOParameters=GPIO_Label
PD13.GPIO_Label=ENCB1
PD13.Signal=S_TIM4_CH2
PD14.GPIOParameters=GPIO_Label
PD14.GPIO_Label=ENCI2
PD14.Signal=GPXTI14
PD15.GPIOParameters=GPIO_Label
PD15.GPIO_Label=TMCUARTTX1
PD15.Mode=Asynchronous
PD15.Signal=UART9_TX
PD2.GPIOParameters=GPIO_PuPd,GPIO_Label
PD2.GPIO_Label=TMCUARTRX2
PD2.GPIO_PuPd=GPIO_NOPULL
PD2.Mode=Asynchronous
PD2.Signal=UART5_RX
PD5.GPIOParameters=GPIO_Label
PD5.GPIO_Label=USBUARTTX
PD5.Mode=Asynchronous
PD5.Signal=USART2_TX
PD6.GPIOParameters=GPIO_Label
PD6.GPIO_Label=USBUARTRX
PD6.Mode=Asynchronous
PD6.Signal=USART2_RX
PD8.GPIOParameters=GPIO_Label
PD8.GPIO_Label=STLK_VCP_RX
PD8.Mode=Asynchronous
PD8.Signal=USART3_TX
PD9.GPIOParameters=GPIO_Label
PD9.GPIO_Label=STLK_VCP_TX
PD9.Mode=Asynchronous
PD9.Signal=USART3_RX
PE0.GPIOParameters=GPIO_PuPd,GPIO_Label
PE0.GPIO_Label=FJOG1
PE0.GPIO_PuPd=GPIO_PULLUP
PE0.Signal=GPIO_Input
PE1.GPIOParameters=GPIO_Label
PE1.GPIO_Label=LED_YELLOW
PE1.Signal=GPIO_Output
PE10.GPIOParameters=GPIO_PuPd,GPIO_Label
PE10.GPIO_Label=FJOG3
PE10.GPIO_PuPd=GPIO_PULLUP
PE10.Signal=GPIO_Input
PE11.GPIOParameters=GPIO_Label
PE11.GPIO_Label=VREFPWM2
PE11.Signal=S_TIM1_CH2
PE12.GPIOParameters=GPIO_PuPd,GPIO_Label
PE12.GPIO_Label=RJOG3
PE12.GPIO_PuPd=GPIO_PULLUP
PE12.Signal=GPIO_Input
PE13.GPIOParameters=GPIO_Label
PE13.GPIO_Label=VREFPWM3
PE13.Signal=S_TIM1_CH3
PE14.GPIOParameters=GPIO_Label
PE14.GPIO_Label=RLIMIT2
PE14.Signal=GPIO_Input
PE15.GPIOParameters=GPIO_PuPd,GPIO_Label
PE15.GPIO_Label=RJOG1
PE15.GPIO_PuPd=GPIO_PULLUP
PE15.Signal=GPIO_Input
PE2.GPIOParameters=GPIO_Label
PE2.GPIO_Label=EIO
PE2.Mode=Full_Duplex_Master
PE2.Signal=SPI4_SCK
PE4.GPIOParameters=GPIO_Label
PE4.GPIO_Label=CLONE3
PE4.Mode=NSS_Signal_Hard_Output
PE4.Signal=SPI4_NSS
PE5.GPIOParameters=GPIO_Label
PE5.GPIO_Label=CLONE1
PE5.Mode=Full_Duplex_Master
PE5.Signal=SPI4_MISO
PE6.GPIOParameters=GPIO_Label
PE6.GPIO_Label=CLONE2
PE6.Mode=Full_Duplex_Master
PE6.Signal=SPI4_MOSI
PE7.GPIOParameters=GPIO_Label
PE7.GPIO_Label=FLIMIT1
PE7.Signal=GPIO_Input
PE8.GPIOParameters=GPIO_Label
PE8.GPIO_Label=RLIMIT1
PE8.Signal=GPIO_Input
PE9.GPIOParameters=GPIO_Label
PE9.GPIO_Label=VREFPWM1
PE9.Signal=S_TIM1_CH1
PF0.GPIOParameters=GPIO_Label
PF0.GPIO_Label=EXTSDA
PF0.Mode=I2C
PF0.Signal=I2C5_SDA
PF1.GPIOParameters=GPIO_Label
PF1.GPIO_Label=EXTSCL
PF1.Mode=I2C
PF1.Signal=I2C5_SCL
PF3.GPIOParameters=GPIO_Label
PF3.GPIO_Label=EN3
PF3.Signal=GPIO_Output
PF4.GPIOParameters=GPIO_Label
PF4.GPIO_Label=DIR2
PF4.Signal=GPIO_Output
PF5.GPIOParameters=GPIO_Label
PF5.GPIO_Label=EN2
PF5.Signal=GPIO_Output
PF6.GPIOParameters=GPIO_Label
PF6.GPIO_Label=EXTRXUART
PF6.Mode=Asynchronous
PF6.Signal=UART7_RX
PF7.GPIOParameters=GPIO_Label
PF7.GPIO_Label=EXTTXUART
PF7.Mode=Asynchronous
PF7.Signal=UART7_TX
PF8.GPIOParameters=GPIO_Label
PF8.GPIO_Label=EXTA1
PF8.Signal=GPIO_Analog
PF9.GPIOParameters=GPIO_Label
PF9.GPIO_Label=EXTA2
PF9.Signal=GPIO_Analog
PG0.GPIOParameters=GPIO_Label
PG0.GPIO_Label=TMCUARTRX1
PG0.Mode=Asynchronous
PG0.Signal=UART9_RX
PG11.GPIOParameters=GPIO_Label
PG11.GPIO_Label=RMII_TX_EN
PG11.Mode=RMII
PG11.Signal=ETH_TX_EN
PG12.GPIOParameters=GPIO_Label
PG12.GPIO_Label=NXT2
PG12.Signal=GPIO_Output
PG13.GPIOParameters=GPIO_Label
PG13.GPIO_Label=RMII_TXD0
PG13.Mode=RMII
PG13.Signal=ETH_TXD0
PG14.GPIOParameters=GPIO_Label
PG14.GPIO_Label=FLIMIT2
PG14.Signal=GPIO_Input
PG6.GPIOParameters=GPIO_Label
PG6.GPIO_Label=DIR1
PG6.Signal=GPIO_Output
PH0-OSC_IN.GPIOParameters=GPIO_Label
PH0-OSC_IN.GPIO_Label=MCO
PH0-OSC_IN.Mode=HSE-External-Clock-Source
PH0-OSC_IN.Signal=RCC_OSC_IN
PH1-OSC_OUT.Signal=RCC_OSC_OUT
RCC.HSE_VALUE=8000000
RCC.SYSCLKFreq_VALUE=550000000
RCC.SYSCLKSource=RCC_SYSCLKSOURCE_PLLCLK
board=NUCLEO-H723ZG
boardIOC=true

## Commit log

2023-05-24 Init commit - scetch of the PCB and empty firmware project
2023-05-24 footprints for serial USB converter and DCDC module
2023-05-25 Nucleo footprint and updates on schematics
2023-05-26 Basic layout of the PCB, encoder connectors added
2023-06-12 partial pin mapping in schematics and cube project
2023-06-13 more connections added to schematic
2023-06-21 labels on buttons on schematics
2023-06-21 added 4, 5, 6, 7 pin JST connectors
2023-07-04 PCB - added VBAT; JST peripherial connectors; power supply capacitors
2023-07-05 tweaks in PCB and fixed rotated nucleo parts in schematic
2023-07-05 Added missing limit switch GPIO and button gpio
2023-07-05 DIR and EN pins connected to GPIO
2023-07-06 First complete version of the PCB
2023-07-06 Revert to 2 layer PCB
2023-07-06 minor tweaks on pcb
2023-07-06 PCB - adjustments and author/date label
2023-07-06 PCB - minor tweaks
2023-07-07 PCB - final version sent to JLCPCB
2023-07-25 First sketches of the firmware
2023-07-26 Tmc and Axis classes, message parsing partial code migration
2023-08-02 Work in progress on command parsing
2023-08-03 Fixes in UART parsing and added control loop. Added missing files
2023-08-03 fixed mixed labeling for jog buttons; initial config of the NXT timers
2023-08-04 develompent of the NXT pulse routines
2023-08-05 nxt and limit switch reading routines are written and optimized
2023-08-07 working UART communication with TMC
2023-08-09 PCB: NXT/DIR external output connectors and some polishing
2023-08-09 filtering capacitors for differential receivers; BOM and placement files for SMD elements
2023-08-10 bugfixes in limit switch reading
2023-08-10 fixed flipped rotation direction relative to stepper 1
2023-08-11 Added voltage shifter between FTDI and board
2023-08-13 universal footprint for UART level shifter
2023-08-15 prototype of the bottom part of the case
2023-08-15 updated bottom part of the case
2023-09-21 minor fixes and optimizations for PCB and bottom case part
2023-09-30 top part of the case, adjustments to the PCB
2023-09-30 basic encoder reading support
2023-10-27 corridor added to the case model
2023-10-27 optimizations in PCB layout made in sync with the design of the case
2023-10-31 updated footprint of Waveshare USB-UART to prevent solder bridging
2023-11-06 last fixes and production files for pcb
2023-11-16 Minor tweaks in the PCB
2023-11-16 Encoder reading support in firmware
2023-11-17 docs added
2023-11-17 fixed typo in schematics
2023-11-17 Updates in docs
2024-02-05 updated BOM and CPL files
2024-03-02 updated case for new PCB; some minor tweaks
2024-03-04 manual for soldering
2024-03-04 fixed bugs (uninitialized timer handle; wrong comparison on encoder overflow)
2024-03-08 Fixed and tested encoder support
2024-03-08 migration to double floating point data type
2024-03-08 tuned micro usb hole size in the bottom part of the case
2024-03-15 project cleanup - deleted unwanted files, fixed too small filesize of .bin bug
2024-03-15 Fixed compilation problems - removed .cproject from repo
2024-03-15 Readme updated with instructions regarding printf and scanf float support
2024-05-07 DRIVER_ID is now defined as a string instead of int
2024-05-08 New section in the LaTeX documentation about how to use it in pyLUMS software
2024-05-10 encoder reading is also reversed if axis is reversed
2024-05-10 better order of operations when filtering limit switch readings
2024-05-10 minor cleanup; preparing to implement reversed homing
2024-05-10 fixed signedness warning in homing routine
2024-05-10 reverse homing implemented
2024-05-10 minor cleanup in uart parser
2024-10-07 serial port communication migrated to a class
2024-10-07 comms with TMC drivers migrated to serial port class
2024-10-07 added commands for tmc driver status, tmc EN pin cycle (error reset) and time from boot
2024-10-08 docs update relating TMC status register reading
2025-01-13 fixed docs latex and pdf
2025-01-13 fixed typo in docs
2025-07-17 PCB updated to use active and available components; added mpn numbers
2025-07-17 updated soldering instructions
2025-07-17 reverted DNP flag for 3V battery
2025-07-17 non-standard components marked as DNP for easier assembly ordering
2025-08-25 removed old gerber and BOM files, please export from kicad
2025-08-25 Revise README.md for STM32CubeIDE compilation steps
2025-08-25 README - add instruction about stlink update
2025-08-25 Fix numbering and clarify instructions in README
2025-08-25 Update connection instructions for micro USB port
2025-08-25 Add disclaimer for STM32CubeIDE instructions
2025-08-25 Fix file extension and improve instructions in README
    Updated file references and instructions for clarity.
2025-08-25 updated symbol for level shifter
